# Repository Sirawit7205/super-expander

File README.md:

# super-expander
What if ATtiny85 has 512 IO pins...

There is a cheap Chinese 16-bit IO Expander chip called AW9523B. 4 of these could be put on the same I2C bus.

With one 8-channel I2C switch PCA9548, you can put 32 AW9523B together, resulting in *32x16 = 512 IO pins*

Experiment on very dense PCB routing, busy I2C bus, new 4 layers PCB promotion on JLCPCB, and my skill to solder QFN/0402 packages.

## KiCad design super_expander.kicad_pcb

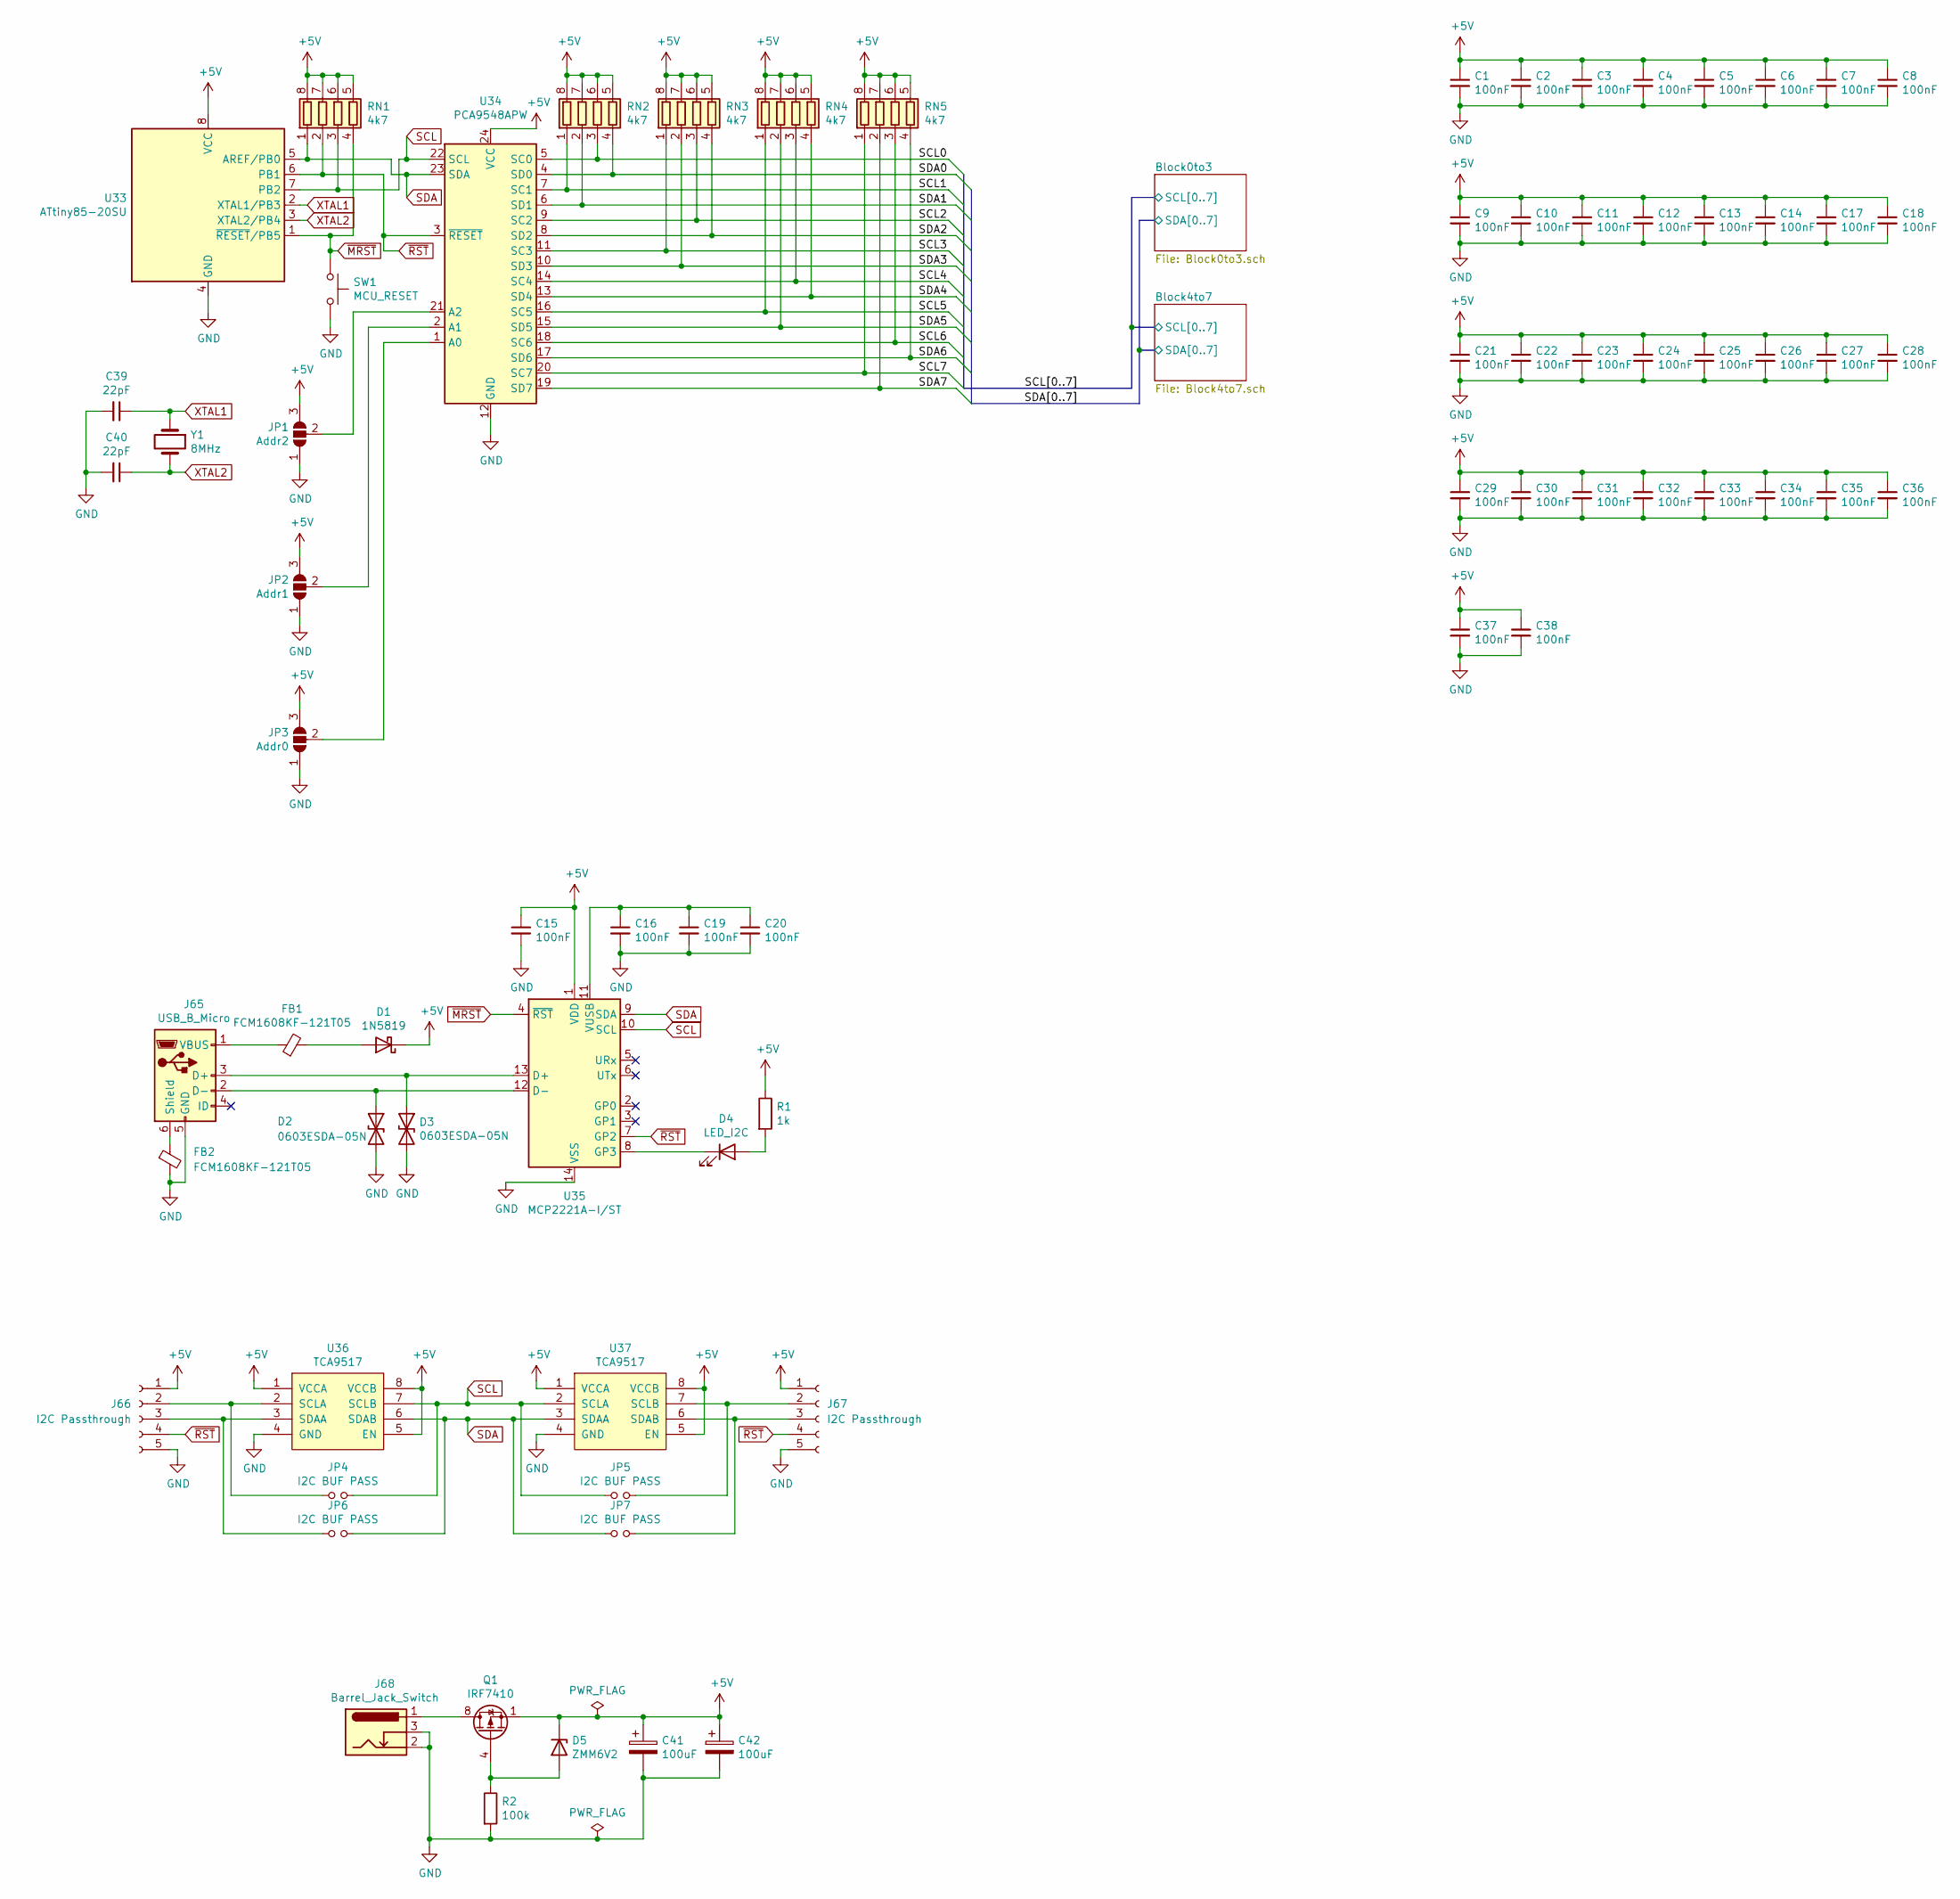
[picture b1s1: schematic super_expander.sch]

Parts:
C1, C2, C3, C4, C5, C6, C7, C8, C9, C10, C11, C12, C13, C14, C15, C16, C17, C18, C19, C20, C21, C22, C23, C24, C25, C26, C27, C28, C29, C30, C31, C32, C33, C34, C35, C36, C37, C38: 100nF; C_0603_1608Metric
C39, C40: 22pF; C_0603_1608Metric
C41, C42: 100uF; CP_Radial_D6.3mm_P2.50mm
D1: 1N5819; D_SOD-123F
D2, D3: 0603ESDA-05N; D_0603_1608Metric
D4: LED_I2C; LED_0603_1608Metric
D5: ZMM6V2; D_MiniMELF
FB1, FB2: FCM1608KF-121T05; L_0603_1608Metric
J65: USB_B_Micro; USB_Micro-B_Molex_47346-0001
J66, J67: I2C Passthrough; PinHeader_1x05_P2.54mm_Vertical
J68: Barrel_Jack_Switch; BarrelJack_Horizontal
JP1: Addr2; SolderJumper-3_P1.3mm_Open_RoundedPad1.0x1.5mm
JP2: Addr1; SolderJumper-3_P1.3mm_Open_RoundedPad1.0x1.5mm
JP3: Addr0; SolderJumper-3_P1.3mm_Open_RoundedPad1.0x1.5mm
JP4, JP5, JP6, JP7: I2C BUF PASS; R_0402_1005Metric
Q1: IRF7410; SOIC-8_3.9x4.9mm_P1.27mm
R1: 1k; R_0603_1608Metric
R2: 100k; R_0603_1608Metric
RN1, RN2, RN3, RN4, RN5: 4k7; R_Array_Convex_4x0603
SW1: MCU_RESET; TS-1101
U33: ATtiny85-20SU; SOIJ-8_5.3x5.3mm_P1.27mm
U34: PCA9548APW; TSSOP-24_4.4x7.8mm_P0.65mm
U35: MCP2221A-I/ST; TSSOP-14_4.4x5mm_P0.65mm
U36, U37: TCA9517; VSSOP-8_3.0x3.0mm_P0.65mm
Y1: 8MHz; Crystal_SMD_5032-2Pin_5.0x3.2mm

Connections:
+5V: C1.1, C2.1, C3.1, C4.1, C5.1, C6.1, C7.1, C8.1, C9.1, C10.1, C11.1, C12.1, C13.1, C14.1, C15.1, C17.1, C18.1, C21.1, C22.1, C23.1, C24.1, C25.1, C26.1, C27.1, C28.1, C29.1, C30.1, C31.1, C32.1, C33.1, C34.1, C35.1, C36.1, C37.1, C38.1, C41.1, C42.1, D1.1 (K), D5.1 (K), J66.1, J67.1, JP1.3 (B), JP2.3 (B), JP3.3 (B), Q1.1 (S), Q1.2 (S), Q1.3 (S), R1.1, RN1.5 (R4.2), RN1.6 (R3.2), RN1.7 (R2.2), RN1.8 (R1.2), RN2.5 (R4.2), RN2.6 (R3.2), RN2.7 (R2.2), RN2.8 (R1.2), RN3.5 (R4.2), RN3.6 (R3.2), RN3.7 (R2.2), RN3.8 (R1.2), RN4.5 (R4.2), RN4.6 (R3.2), RN4.7 (R2.2), RN4.8 (R1.2), RN5.5 (R4.2), RN5.6 (R3.2), RN5.7 (R2.2), RN5.8 (R1.2), U33.8 (VCC), U34.24 (VCC), U35.1 (VDD), U36.1 (VCCA), U36.5 (EN), U36.8 (VCCB), U37.1 (VCCA), U37.5 (EN), U37.8 (VCCB); also elsewhere on the board
/SCL0: RN2.3 (R3.1), U34.5 (SC0); also elsewhere on the board
/SCL1: RN2.1 (R1.1), U34.7 (SC1); also elsewhere on the board
/SCL2: RN3.3 (R3.1), U34.9 (SC2); also elsewhere on the board
/SCL3: RN3.1 (R1.1), U34.11 (SC3); also elsewhere on the board
/SCL4: RN4.3 (R3.1), U34.14 (SC4); also elsewhere on the board
/SCL5: RN4.1 (R1.1), U34.16 (SC5); also elsewhere on the board
/SCL6: RN5.3 (R3.1), U34.18 (SC6); also elsewhere on the board
/SCL7: RN5.1 (R1.1), U34.20 (SC7); also elsewhere on the board
/SDA0: RN2.4 (R4.1), U34.4 (SD0); also elsewhere on the board
/SDA1: RN2.2 (R2.1), U34.6 (SD1); also elsewhere on the board
/SDA2: RN3.4 (R4.1), U34.8 (SD2); also elsewhere on the board
/SDA3: RN3.2 (R2.1), U34.10 (SD3); also elsewhere on the board
/SDA4: RN4.4 (R4.1), U34.13 (SD4); also elsewhere on the board
/SDA5: RN4.2 (R2.1), U34.15 (SD5); also elsewhere on the board
/SDA6: RN5.4 (R4.1), U34.17 (SD6); also elsewhere on the board
/SDA7: RN5.2 (R2.1), U34.19 (SD7); also elsewhere on the board
GND: C1.2, C2.2, C3.2, C4.2, C5.2, C6.2, C7.2, C8.2, C9.2, C10.2, C11.2, C12.2, C13.2, C14.2, C15.2, C16.2, C17.2, C18.2, C19.2, C20.2, C21.2, C22.2, C23.2, C24.2, C25.2, C26.2, C27.2, C28.2, C29.2, C30.2, C31.2, C32.2, C33.2, C34.2, C35.2, C36.2, C37.2, C38.2, C39.2, C40.2, C41.2, C42.2, D2.2 (A2), D3.2 (A2), FB2.2, J65.5 (GND), J66.5, J67.5, J68.2, J68.3, JP1.1 (A), JP2.1 (A), JP3.1 (A), R2.2, SW1.2, U33.4 (GND), U34.12 (GND), U35.14 (VSS), U36.4 (GND), U37.4 (GND); also elsewhere on the board
unnamed: C16.1, C19.1, C20.1, U35.11 (VUSB)
unnamed: D1.2 (A), FB1.2
unnamed: D2.1 (A1), J65.2 (D-), U35.12 (D-)
unnamed: D3.1 (A1), J65.3 (D+), U35.13 (D+)
unnamed: D4.1 (K), U35.8 (GP3)
unnamed: D4.2 (A), R1.2
unnamed: D5.2 (A), Q1.4 (G), R2.1
unnamed: FB1.1, J65.1 (VBUS)
unnamed: FB2.1, J65.6 (Shield)
unnamed: J66.2, JP4.1, U36.2 (SCLA)
unnamed: J66.3, JP6.1, U36.3 (SDAA)
unnamed: J67.2, JP5.2, U37.7 (SCLB)
unnamed: J67.3, JP7.2, U37.6 (SDAB)
unnamed: J68.1, Q1.5 (D), Q1.6 (D), Q1.7 (D), Q1.8 (D)
unnamed: JP1.2 (C), U34.21 (A2)
unnamed: JP2.2 (C), U34.2 (A1)
unnamed: JP3.2 (C), U34.1 (A0)
SCL: JP4.2, JP5.1, RN1.3 (R3.1), U33.7 (PB2), U34.22 (SCL), U35.10 (SCL), U36.7 (SCLB), U37.2 (SCLA)
SDA: JP6.2, JP7.1, RN1.1 (R1.1), U33.5 (AREF/PB0), U34.23 (SDA), U35.9 (SDA), U36.6 (SDAB), U37.3 (SDAA)
XTAL1: C39.1, U33.2 (XTAL1/PB3), Y1.1
XTAL2: C40.1, U33.3 (XTAL2/PB4), Y1.2
~MRST: RN1.4 (R4.1), SW1.1, U33.1 (~RESET~/PB5), U35.4 (~RST)
~RST: J66.4, J67.4, RN1.2 (R2.1), U33.6 (PB1), U34.3 (~RESET), U35.7 (GP2); also elsewhere on the board
